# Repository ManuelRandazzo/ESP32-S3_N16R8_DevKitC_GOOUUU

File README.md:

# ESP32-S3_N16R8_DevKit_GOOUUU

---

## Overview

This repository collects all hardware design resources related to the **GOOUUU ESP32-S3 N16R8 DevKitC-1**, created because no complete public reference for this board was available online.

The goal of this repository is to centralize electronic, mechanical, and firmware-related assets required for:

- Hardware integration
- Firmware development
- Custom PCB design
- Enclosure design
- Documentation reference

All files are organized to provide a single source of truth for developers working with this specific board variant.

---

## Full KiCAD Library

**KiCAD Version Used : 10.0.1-2**

The directory "**KiCAD_Lib_ESP32-S3**" contains these files of the Board :
- **3D_CAD**
- **Footprint**
- **SymbolSchematic**

You can just add the directory "**KiCAD_Lib_ESP32-S3**" wherever you want in your device and than update the "fp-lib-table", the "sym-lib-table" and then choose the right 3D file of the board.
(Tip : It is recommended to use **Relatives paths** insted of Absolutes paths. To do this make sure to write ***${KIPRJMOD}/../*** at the start of the directories names if you'll include the library in the project folder)

**How To Do It**

- **Copy-Paste** the "KiCAD_Lib_ESP32-S3" directory wherever you want, e.g. in your KiCAD project directory and remember or copy this new path.

- **Open** your KiCAD project (File name : ***yourPrjName.kicad_pro***)

- To add the **Schematic** to the "sym-lib-table" : ***Preferences*** -> ***Manage Symbol Libraries*** -> ***Project Specific Libraries*** (or the *Global Libraries* if you prefer) -> click **+** -> Give it a name and choose the path of the ***KiCAD_Lib_ESP32-S3/SymbolSchematic/ComponentsLibraryESP32-S3.kicad_sym*** directory.

- To add the **Footprint** to the "fp-lib-table" : ***Preferences*** -> ***Manage Footprints Libraries*** -> ***Project Specific Libraris*** (or the *Global Libraries* if you prefer) -> click **+** -> Give it a name and choose the path of the ***KiCAD_Lib_ESP32-S3/Footprint/ESP32-S3-N16R8_GOOUUU.pretty*** directory.

---

## 3D Models

Contains mechanical models of the board used for enclosure design and mechanical integration.

- `STEP` files — CAD models compatible with Fusion360, SolidWorks, FreeCAD, and similar software.

Typical use cases:

- mounting alignment
- mechanical integration
- project visualization

Two variants of the 3D model are provided:

<p align="center">
  <em><strong>Left: board only — Right: board with socket headers allowing module removal</em>
</p>

---

### Top and Bottom Views

<p align="center">
  <em><strong>Left: top view of the board — Right: bottom view of the board</em>
</p>

---

## PCB Footprints

Library footprints representing the **GOOUUU ESP32-S3 N16R8 DevKitC-1 module**.

Includes:

- PCB land patterns
- pin definitions
- mechanical outlines
- pin labeling
- USB Type-C identification (**OTG** or **TTL/UART**)

These footprints are intended for reuse in custom PCB designs and mechanical integrations.

<p align="center">
  <em><strong>TODO: add board components to the footprint</em>
</p>

---

## PCB Schematics

Schematic symbol exposing all available board pins for direct integration into custom designs.

---

## Hardware Design Notes

Some pins require special attention because improper usage may cause boot failures or unstable behavior.

The ESP32-S3 uses **strapping pins**, which define the boot configuration during power-up.

Avoid connecting external devices that force these pins HIGH or LOW during reset.

### Relevant strapping pins

- **GPIO0** — Boot pin. Hold LOW to enter download (bootloader) mode.  
  Normally not required unless firmware prevents flashing.

- **GPIO3** — JTAG-related pin.  
  The ESP32-S3 includes a built-in USB-JTAG debugger accessible directly via the USB-C port.  
  PlatformIO configuration guide:  
  https://community.platformio.org/t/how-to-use-jtag-built-in-debugger-of-the-esp32-s3-in-platformio/36042

- **GPIO45** — May interfere with SPI devices during flashing if externally driven.

- **GPIO46** — UART log output used for:
  - `printf()`
  - `ESP_LOGx`
  - ROM boot messages
  - panic handler output
  - crash dumps
  - firmware flashing

<p align="center">
  <em><strong>Board pinout reference</em>
</p>

---

## PCB Routing (TODO)

A routing reference found online is included for documentation purposes:

https://github.com/ManuelRandazzo/ESP32-S3_N16R8_DevKit_GOOUUU/tree/main/RepoFiles/images/DevKitRouting.png

The KiCad project is available in this repository.  
Contributions improving the routing are welcome.

---

## PlatformIO and Pioarduino Board Configuration
### PlatformIO Board Configuration
Original Author of this configuration : https://github.com/sivar2311/ESP32-PlatformIO-Flash-and-PSRAM-configurations.

CUSTOM Config -> **flash_mode** from "opi" to "qio" to be coerent with the pioarduino configuration
```ini
; Flash: 16MB OT, PSRAM: 8MB OT
[env:esp32-s3-devkitc-1]
platform = espressif32
board = esp32-s3-devkitc-1
framework = arduino

board_build.arduino.memory_type = opi_opi
board_build.flash_mode = qio ; CUSTOM -> before was "opi"
board_build.psram_type = opi
board_upload.flash_size = 16MB
board_upload.maximum_size = 16777216
board_build.partitions = default_16MB.csv
board_build.extra_flags = 
  -DBOARD_HAS_PSRAM
  -mfix-esp32-psram-cache-issue
```

---

### Pioarduino Board Configuration (PlatformIO Fork)
Original Author of this configuration : https://github.com/sivar2311/platformio_boards/blob/main/esp32-s3-devkitc1-n16r8.json
```ini
; Flash: 16MB OT, PSRAM: 8MB OT
[env:esp32-s3-devkitc1-n16r8]
platform = https://github.com/pioarduino/platform-espressif32/releases/download/stable/platform-espressif32.zip
framework = arduino
board = esp32-s3-devkitc1-n16r8
board_build.extra_flags = 
  -mfix-esp32-psram-cache-issue
```

---

### Add Builtin Debugger for PlatformIO and Pioarduino Fork via Native USB (OTG)
Under the previously configured "board_build.extra_flags" add :
```ini
; Debugger setup link: https://community.platformio.org/t/how-to-use-jtag-built-in-debugger-of-the-esp32-s3-in-platformio/36042
debug_tool = esp-builtin
build_type = debug
debug_load_mode = modified ; To recompile only the most recent changes (faster than recompile all files)
;debug_init_break = thb setup ; OPTIONAL : Change it to start the debugger from the function that you prefer, default is function "main"
```

---

### Add Firmware Flashing, Debugging and Logging PlatformIO and Pioarduino Fork
The ESP32-S3 has a builtin **USB Serial/JTAG Controller ROM bootloader** over native USB (port labeled as OTG) which is used to do multiple tasks such as flashing the firmware, debugging, logging and other things using just one USB 2.0 port.

> [!WARNING]
> When using the USB CDC, the USB OTG will no longer be available.

Under the previously configured "board_build.extra_flags" add :
```ini
; Debugger setup link: https://community.platformio.org/t/how-to-use-jtag-built-in-debugger-of-the-esp32-s3-in-platformio/36042
debug_tool = esp-builtin
build_type = debug
debug_load_mode = modified ; To recompile only the most recent changes (faster than recompile all files especially the external libraries)
;debug_init_break = thb setup ; OPTIONAL : Change it to start the debugger from the function that you prefer, default is function "main"

; Serial port redirected to USB CDC instead of UART
build_flags =
    -D ARDUINO_USB_MODE=1 ; Select the USB CDC (Communication Device Class) instead of UART ---> WARNING : USB OTG is no longer available
    -D ARDUINO_USB_CDC_ON_BOOT=1 ; Automatically opens the serial port after the firmware upload
```

<p>
  <em><strong>Note : Debugging sessions can coexist with logging via USB CDC</em>
</p>

---

## Arduino Board Configuration

**Board selection**
```C
ESP32S3 Dev Module
```
**Configuration reference:**
https://www.reddit.com/r/esp32/comments/1h09gyy/how_to_configure_esp32_s3_n16r8_in_arduino_ide/

---

## Usage

You are free to use, clone, modify, and integrate the content of this repository.

Suggestions and improvements are welcome.

---

## Legal Notice

This project is not affiliated with, endorsed by, or sponsored by GOOUUU Tech.

KiCad schematic symbols and PCB layouts were independently created by Manuel Randazzo based on visual inspection and reverse engineering of the GOOUUU ESP32-S3 N16R8 DevKit module.

GOOUUU Tech remains the manufacturer and owner of the original hardware design.

This repository exists for educational and community purposes only.
If requested by GOOUUU Tech, the repository contents will be removed.

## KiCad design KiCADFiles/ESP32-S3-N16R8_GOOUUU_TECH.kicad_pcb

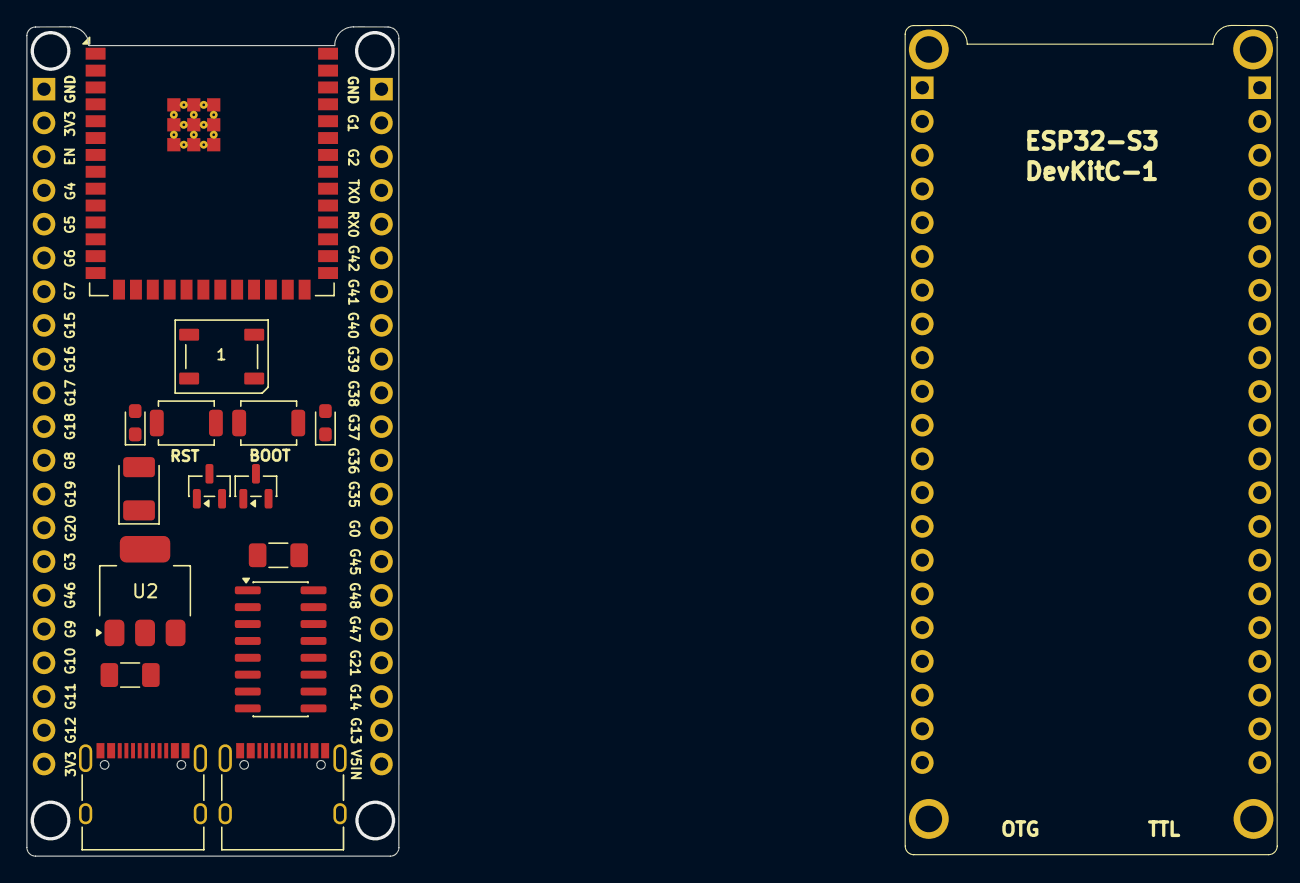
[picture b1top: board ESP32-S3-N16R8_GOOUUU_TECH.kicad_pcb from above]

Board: 2 copper layers, 28.0 x 62.4 mm, 17 parts (0 on the bottom side), 5 nets, no tracks yet.

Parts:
BOOT1: SW_Push; SW_SPST_TS-1088-xR025
C1, C3: C; C_1206_3216Metric_Pad1.33x1.80mm_HandSolder
C2: C_Polarized; CP_EIA-3528-21_Kemet-B_HandSolder
D1, D2: LED; LED_0603_1608Metric_Pad1.05x0.95mm_HandSolder
D3: WS2812B; LED_WS2812B_PLCC4_5.0x5.0mm_P3.2mm
J2, J2#2: Conn_01x21; PinHeader_1x21_P2.54mm_Vertical
P1, P2: USB_C_Plug; USB_C_Receptacle_XKB_U262-16XN-4BVC11
Q3, Q4: SS8050; SOT-23
RST1: SW_Push; SW_SPST_TS-1088-xR025
U1: CH340C; SOIC-16_3.9x9.9mm_P1.27mm
U2: AMS1117; SOT-223-3_TabPin2
U3: ESP32-S3-WROOM-2

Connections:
unnamed: P1.A1 (GND), P1.A12 (GND), P1.B1 (GND), P1.B12 (GND)
unnamed: P1.A4 (VBUS), P1.A9 (VBUS), P1.B4 (VBUS), P1.B9 (VBUS)
unnamed: P2.A1 (GND), P2.A12 (GND), P2.B1 (GND), P2.B12 (GND)
unnamed: P2.A4 (VBUS), P2.A9 (VBUS), P2.B4 (VBUS), P2.B9 (VBUS)
unnamed: U3.1 (GND), U3.40 (GND), U3.41 (GND)
